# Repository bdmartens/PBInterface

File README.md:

# PBInterface
Pixelblaze v3 interface board/box
These are all the files I used to make a pixelblaze v3 controller interface board and controller box.
My intended purpose was an interactive project box for my kids.

The PCB allows interfacing with the board hard button (used to toggle between patterns, fairly hard-coded to the project), as well as GPIO 25 and 26 - which are pulled to ground by a button press.
It also exposes GPIO33, which allows for analog read.  Using a 102 trim pot resistor, this can be is pulled up to 3.3v.  My use case was with a pressure-sensitive strip, to be used as a mattress pressure sensor, so that my kids could make patterns that interacted with them being in their bed or not.

There is also place for an electrolytic capacitor - not sure if it is needed, but I went with a fairly beefy 1000 uf cap to keep power even given my amazon-purchased power supply.

The hard button and GPIO 33 are only accessible via a contact pad on the back of the pixelblaze v3, and as such would need to be hand-soldered via a wire between the pixelblaze and the interface board. 

Otherwise, solder header pins in for th epower connection, reset/hard button, and button 25/26.  I have a terminal block on mine to connect to the sensor strip (in the photo, hidden under the power socket wires)
There is also a header for a power switch, which I use a mini toggle switch.

I have also included the fusion 360 PCB box project file, as well as a step file, with most of the parameters set as variables that can be modified as needed.
The box holes are sized to hava M2 bolts used, but this can also be modified in the fusion 360 parameters.

Pressure-sensitive strip: https://www.amazon.ca/LANTRO-JS-Pressure-Intelligent-Breathing/dp/B09C8TVYTR?pd_rd_w=SZxXu

5V Power adapter - https://www.amazon.ca/BTF-LIGHTING-Plastic-Adapter-Transformer-WS2812B/dp/B01D8FM71S?pd_rd_w=SZxXu

Power socket - https://www.amazon.ca/gp/product/B01M0RFV34

Momentary buttons - https://www.amazon.ca/gp/product/B07FKB6648

Power switch - https://www.amazon.ca/gp/product/B00F4MG7HY

----
More specifics about the pixelblaze GPIO pins available here: https://electromage.com/docs/GPIO

Learn more about Pixelblaze here: https://electromage.com/

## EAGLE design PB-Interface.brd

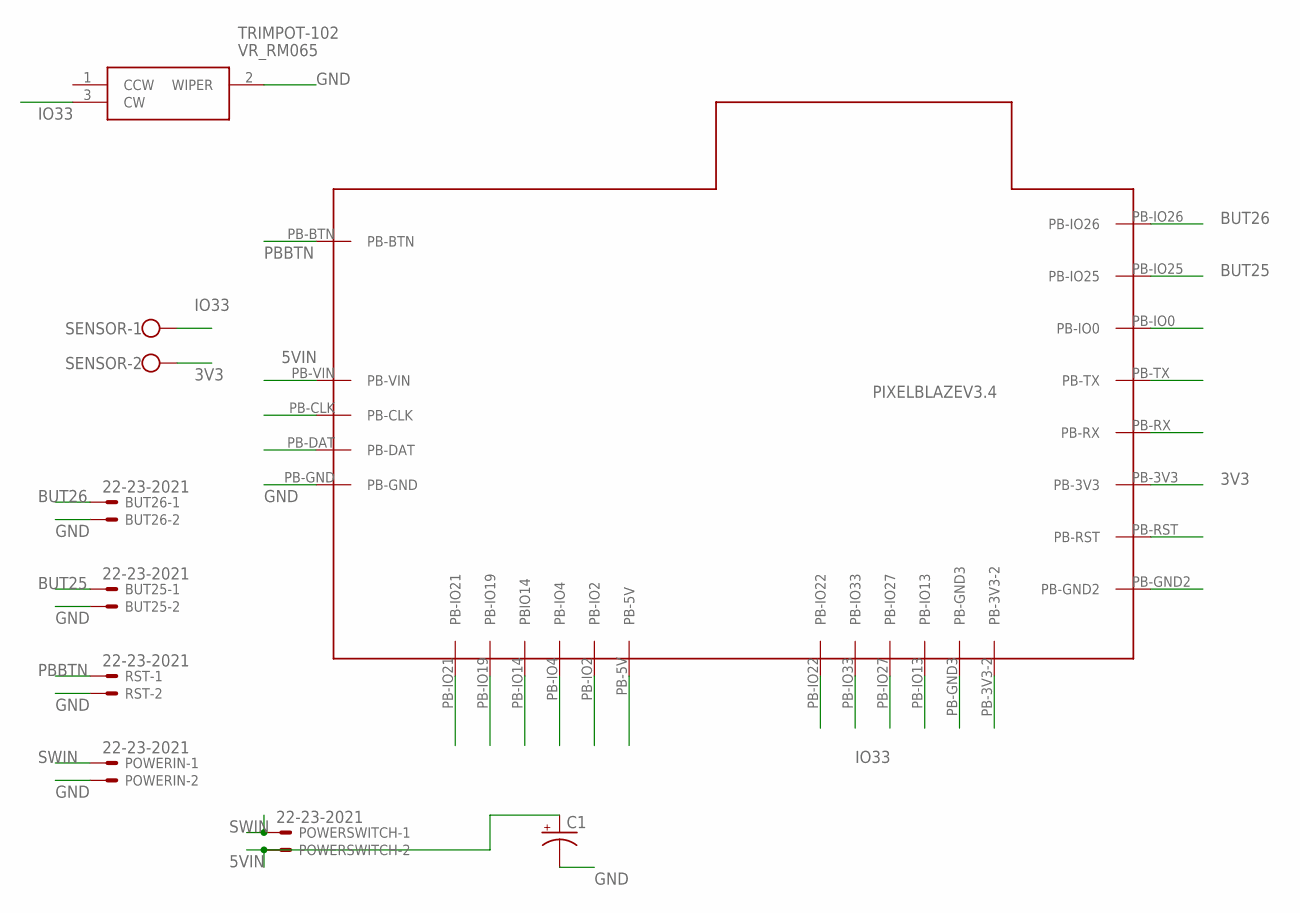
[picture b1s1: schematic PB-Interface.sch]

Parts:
BUT25, BUT26: 22-23-2021
C1: CPOL-USE5-10.5; E5-10,5
PIXELBLAZEV3.4: PIXELBLAZE-V3.4; PIXELBLAZE-V3
POWERIN: 22-23-2021
POWERSWITCH: 22-23-2021
RST: 22-23-2021
SENSOR: W237-102
TRIMPOT-102: VR_RM065; VRRM065

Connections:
3V3: PIXELBLAZEV3.4.PB-3V3, SENSOR.2
5VIN: C1.+, PIXELBLAZEV3.4.PB-VIN, POWERSWITCH.2
BUT25: BUT25.1, PIXELBLAZEV3.4.PB-IO25
BUT26: BUT26.1, PIXELBLAZEV3.4.PB-IO26
GND: BUT25.2, BUT26.2, C1.-, PIXELBLAZEV3.4.PB-GND, POWERIN.2, RST.2, TRIMPOT-102.2 (WIPER)
IO33: PIXELBLAZEV3.4.PB-IO33, SENSOR.1, TRIMPOT-102.3 (CW)
PBBTN: PIXELBLAZEV3.4.PB-BTN, RST.1
SWIN: POWERIN.1, POWERSWITCH.1

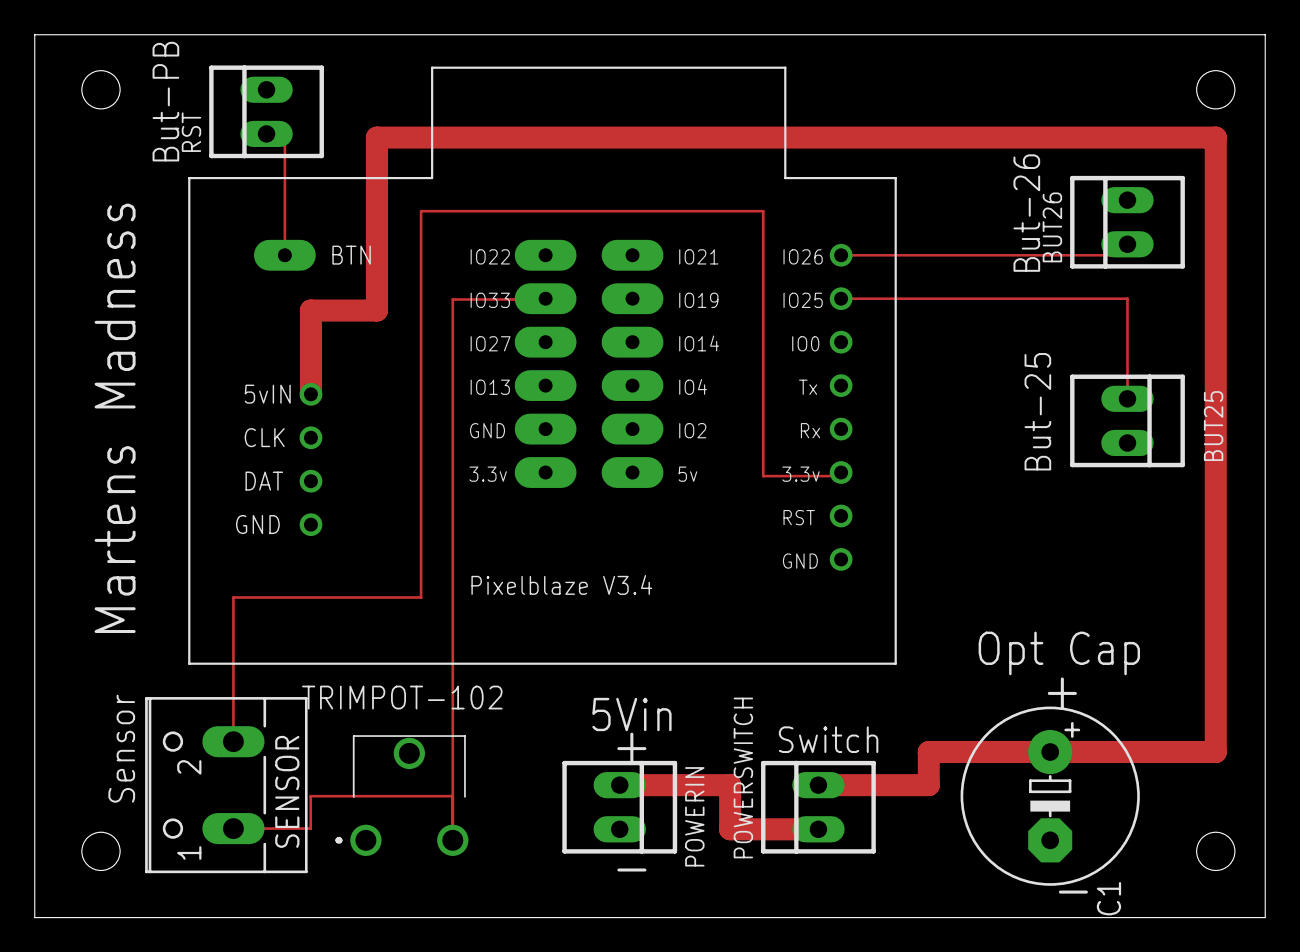
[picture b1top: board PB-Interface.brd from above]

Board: 2 copper layers, 70.8 x 50.8 mm, 9 parts (0 on the bottom side), 8 nets.
